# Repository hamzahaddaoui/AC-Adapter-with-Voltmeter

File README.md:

# AC-Adapter-with-Voltmeter

The project's purpose was to build an AC adapter using linear components (7805 and LM317), since it is made for hobbystic purposes (low currents are drawn). 
One source of voltage is fixed at 5V and the other can be adjusted (1.2v to 14v) using a potentiometer. 

The second part of the project was building a voltmeter, sensing it using the microcontroller internal ADC (16bit) and showing it on the 7-segments display. 
The accuracy of the voltage measurement is about 0.1V.

### Electronics schematic

### PCB schematic

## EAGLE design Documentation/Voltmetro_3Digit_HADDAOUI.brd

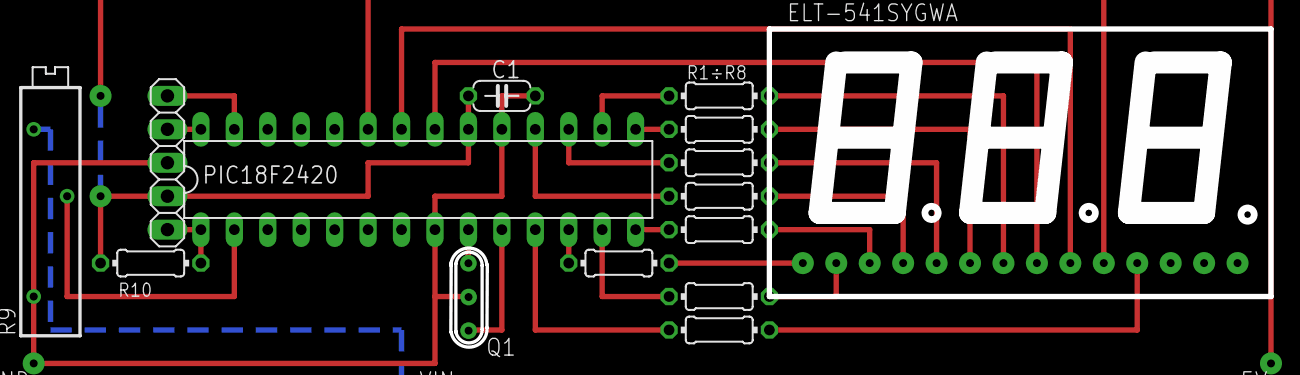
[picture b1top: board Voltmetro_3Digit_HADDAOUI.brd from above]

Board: 2 copper layers, 13 parts (0 on the bottom side), 14 nets.

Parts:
C1: 100n; C050-024X044
JP1: 1X05
PIC18F2420: DIL28-3
R1÷R8, R2, R3, R4, R5, R6, R7, R8: 220; 0204/7
R9: 10K; RTRIM3006P
R10: 10K; 0204/7

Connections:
S$2: PIC18F2420.18, R3.1
S$3: PIC18F2420.17, R7.1
S$4: PIC18F2420.15, R2.1
S$5: PIC18F2420.16, R1÷R8.1
S$15: C1.1, R10.1
S$16: C1.2, JP1.3, PIC18F2420.19, R9.1
S$19: PIC18F2420.11, R8.1
S$22: PIC18F2420.12, R5.1
S$23: PIC18F2420.13, R6.1
S$24: PIC18F2420.14, R4.1
S$30: JP1.4, PIC18F2420.28
S$31: JP1.5, PIC18F2420.27
S$33: JP1.1, PIC18F2420.1, R10.2
S$34: PIC18F2420.2, R9.2
